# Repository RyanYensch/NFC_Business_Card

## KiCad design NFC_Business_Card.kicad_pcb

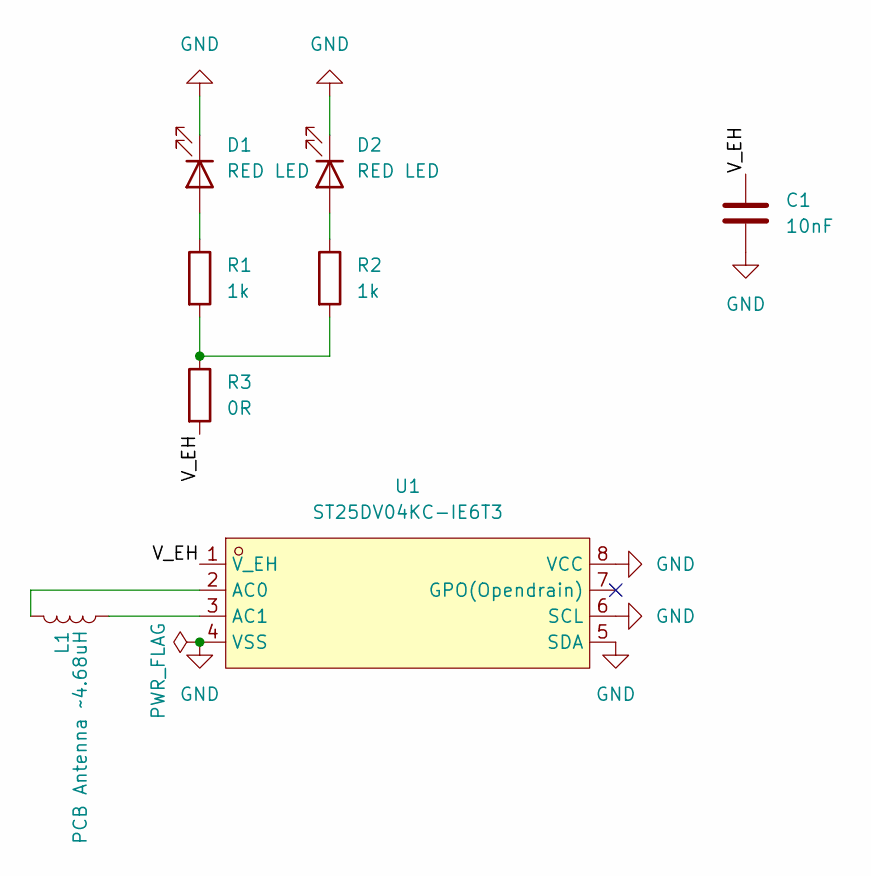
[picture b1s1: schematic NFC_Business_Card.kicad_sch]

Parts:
C1: 10nF; C_0603_1608Metric
D1, D2: RED LED; LED_0603_1608Metric
L1: PCB Antenna ~4.68uH; NFC_80x50_5T
R1, R2: 1k; R_0603_1608Metric; LCSC C21190
R3: 0R; R_0603_1608Metric
U1: ST25DV04KC-IE6T3; TSSOP-8_4.4x3mm_P0.65mm; MPN ST25DV04KC-IE6T3; LCSC Part C5221719

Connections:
/V_EH: C1.2, R3.2, U1.1 (V_EH)
GND: C1.1, D1.1 (K), D2.1 (K), U1.4 (VSS), U1.5 (SDA), U1.6 (SCL), U1.8 (VCC)
unnamed: D1.2 (A), R1.1
unnamed: D2.2 (A), R2.1
unnamed: R1.2, R2.2, R3.1
unnamed: L1.2, U1.2 (AC0)
unnamed: L1.1, U1.3 (AC1)

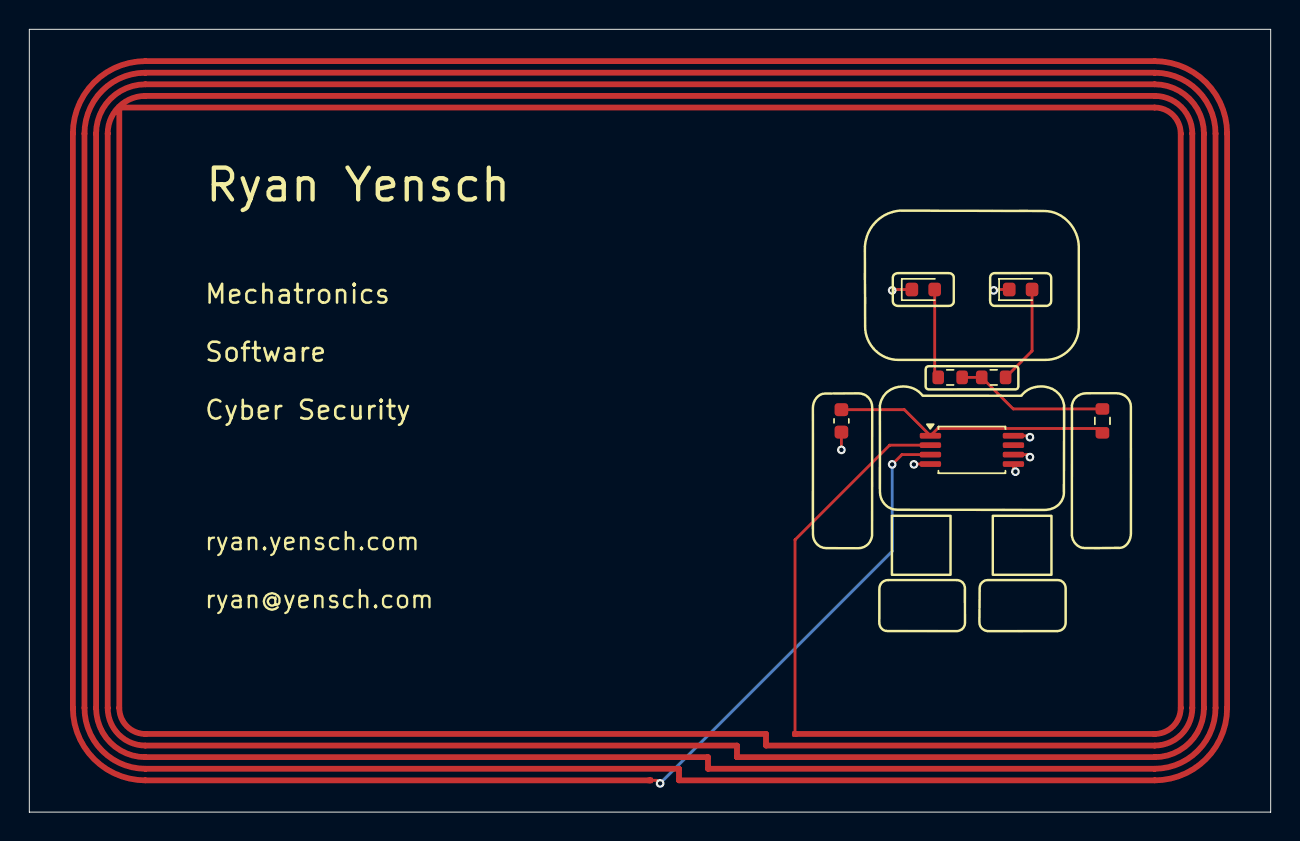
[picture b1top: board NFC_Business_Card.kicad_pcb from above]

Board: 2 copper layers, 85.6 x 54.0 mm, 8 parts (0 on the bottom side), 7 nets.

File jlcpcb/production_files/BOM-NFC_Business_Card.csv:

Comment,Designator,Footprint,LCSC,Quantity
0R,R3,R_0603_1608Metric,C21189,1
10nF,C1,C_0603_1608Metric,C57112,1
1k,"R1,R2",R_0603_1608Metric,C21190,2
RED LED,"D1,D2",LED_0603_1608Metric,C2286,2
ST25DV04KC-IE6T3,U1,TSSOP-8_4.4x3mm_P0.65mm,C5221719,1
